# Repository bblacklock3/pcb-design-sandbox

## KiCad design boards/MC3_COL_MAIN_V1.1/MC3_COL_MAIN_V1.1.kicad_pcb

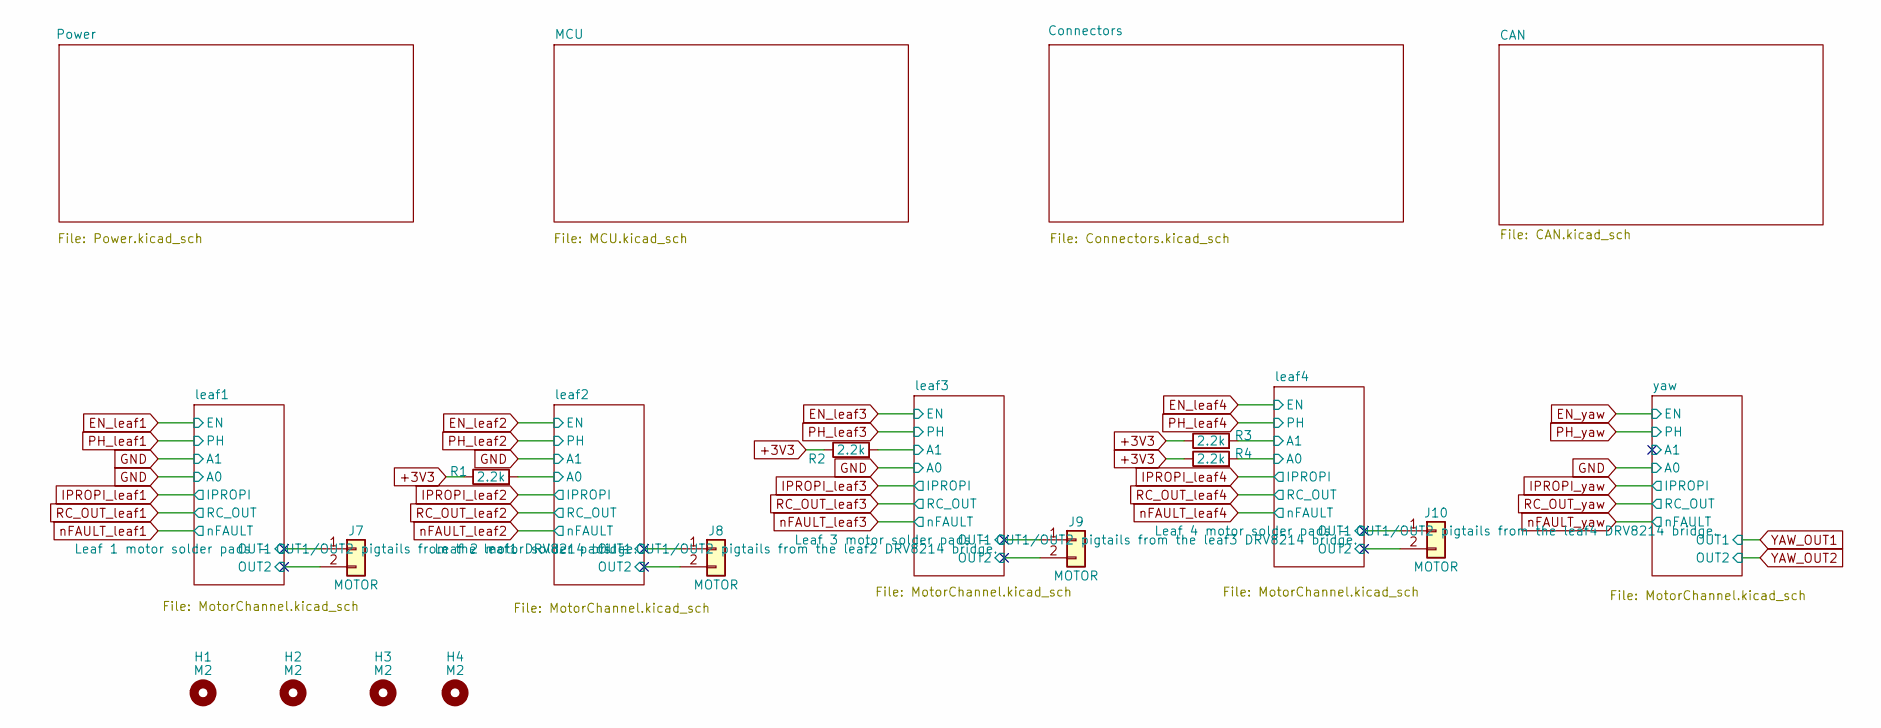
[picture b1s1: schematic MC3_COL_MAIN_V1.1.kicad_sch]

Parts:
H1, H2, H3, H4: M2; MountingHole_2.2mm_M2
J7, J8, J9, J10: MOTOR; SolderPads_2x_2.2x1.4mm_P2.6mm
R1, R2, R3, R4: 2.2k; R_0402_1005Metric; MPN 0402WGF2201TCE; LCSC C25879

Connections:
/leaf1/OUT1: J7.1; also elsewhere on the board
/leaf1/OUT2: J7.2; also elsewhere on the board
/leaf2/A0: R1.2; also elsewhere on the board
/leaf2/OUT1: J8.1; also elsewhere on the board
/leaf2/OUT2: J8.2; also elsewhere on the board
/leaf3/A1: R2.2; also elsewhere on the board
/leaf3/OUT1: J9.1; also elsewhere on the board
/leaf3/OUT2: J9.2; also elsewhere on the board
/leaf4/A0: R4.2; also elsewhere on the board
/leaf4/A1: R3.2; also elsewhere on the board
/leaf4/OUT1: J10.1; also elsewhere on the board
/leaf4/OUT2: J10.2; also elsewhere on the board

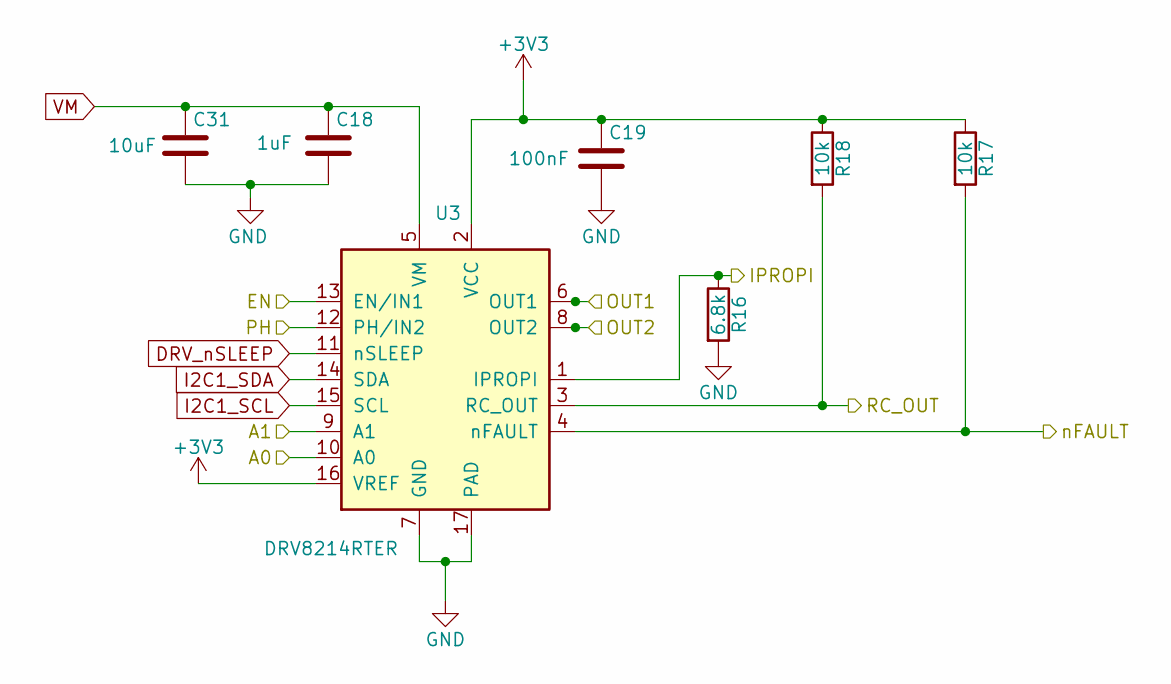
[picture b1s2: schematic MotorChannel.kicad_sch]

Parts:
C18: 1uF; C_0603_1608Metric; MPN CL10A105KB8NNNC; LCSC C15849
C19: 100nF; C_0402_1005Metric; MPN CL05B104KO5NNNC; LCSC C1525
C31: 10uF; C_0805_2012Metric; MPN CL21A106KAYNNNE; LCSC C15850
R16: 6.8k; R_0402_1005Metric; MPN RC0402FR-076K8L; LCSC C93940
R17, R18: 10k; R_0402_1005Metric; MPN 0402WGF1002TCE; LCSC C25744
U3: DRV8214RTER; WQFN-16-1EP_3x3mm_P0.5mm_EP1.68x1.68mm_ThermalVias; MPN DRV8214RTER; LCSC C22427938

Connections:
/leaf1/OUT1: U3.6 (OUT1); also elsewhere on the board
/leaf1/OUT2: U3.8 (OUT2); also elsewhere on the board
DRV_nSLEEP: U3.11 (nSLEEP); also elsewhere on the board
EN_leaf1: U3.13 (EN/IN1); also elsewhere on the board
I2C1_SCL: U3.15 (SCL); also elsewhere on the board
I2C1_SDA: U3.14 (SDA); also elsewhere on the board
IPROPI_leaf1: R16.1, U3.1 (IPROPI); also elsewhere on the board
PH_leaf1: U3.12 (PH/IN2); also elsewhere on the board
RC_OUT_leaf1: R18.2, U3.3 (RC_OUT); also elsewhere on the board
nFAULT_leaf1: R17.2, U3.4 (nFAULT); also elsewhere on the board

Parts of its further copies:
C20, C22, C24, C26: 1uF; C_0603_1608Metric; MPN CL10A105KB8NNNC; LCSC C15849
C21, C23, C25, C27: 100nF; C_0402_1005Metric; MPN CL05B104KO5NNNC; LCSC C1525
C33, C34, C35, C36: 10uF; C_0805_2012Metric; MPN CL21A106KAYNNNE; LCSC C15850
R19, R22, R25, R28: 6.8k; R_0402_1005Metric; MPN RC0402FR-076K8L; LCSC C93940
R20, R21, R23, R24, R26, R27, R29, R30: 10k; R_0402_1005Metric; MPN 0402WGF1002TCE; LCSC C25744
U4, U5, U6, U7: DRV8214RTER; WQFN-16-1EP_3x3mm_P0.5mm_EP1.68x1.68mm_ThermalVias; MPN DRV8214RTER; LCSC C22427938

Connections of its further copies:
/leaf2/A0: U4.10 (A0); also elsewhere on the board
/leaf2/OUT1: U4.6 (OUT1); also elsewhere on the board
/leaf2/OUT2: U4.8 (OUT2); also elsewhere on the board
/leaf3/A1: U5.9 (A1); also elsewhere on the board
/leaf3/OUT1: U5.6 (OUT1); also elsewhere on the board
/leaf3/OUT2: U5.8 (OUT2); also elsewhere on the board
/leaf4/A0: U6.10 (A0); also elsewhere on the board
/leaf4/A1: U6.9 (A1); also elsewhere on the board
/leaf4/OUT1: U6.6 (OUT1); also elsewhere on the board
/leaf4/OUT2: U6.8 (OUT2); also elsewhere on the board
/yaw/A1: U7.9 (A1)
DRV_nSLEEP: U4.11 (nSLEEP), U5.11 (nSLEEP), U6.11 (nSLEEP), U7.11 (nSLEEP); also elsewhere on the board
EN_leaf2: U4.13 (EN/IN1); also elsewhere on the board
EN_leaf3: U5.13 (EN/IN1); also elsewhere on the board
EN_leaf4: U6.13 (EN/IN1); also elsewhere on the board
EN_yaw: U7.13 (EN/IN1); also elsewhere on the board
I2C1_SCL: U4.15 (SCL), U5.15 (SCL), U6.15 (SCL), U7.15 (SCL); also elsewhere on the board
I2C1_SDA: U4.14 (SDA), U5.14 (SDA), U6.14 (SDA), U7.14 (SDA); also elsewhere on the board
IPROPI_leaf2: R19.1, U4.1 (IPROPI); also elsewhere on the board
IPROPI_leaf3: R22.1, U5.1 (IPROPI); also elsewhere on the board
IPROPI_leaf4: R25.1, U6.1 (IPROPI); also elsewhere on the board
IPROPI_yaw: R28.1, U7.1 (IPROPI); also elsewhere on the board
PH_leaf2: U4.12 (PH/IN2); also elsewhere on the board
PH_leaf3: U5.12 (PH/IN2); also elsewhere on the board
PH_leaf4: U6.12 (PH/IN2); also elsewhere on the board
PH_yaw: U7.12 (PH/IN2); also elsewhere on the board
RC_OUT_leaf2: R21.2, U4.3 (RC_OUT); also elsewhere on the board
RC_OUT_leaf3: R24.2, U5.3 (RC_OUT); also elsewhere on the board
RC_OUT_leaf4: R27.2, U6.3 (RC_OUT); also elsewhere on the board
RC_OUT_yaw: R30.2, U7.3 (RC_OUT); also elsewhere on the board
YAW_OUT1: U7.6 (OUT1); also elsewhere on the board
YAW_OUT2: U7.8 (OUT2); also elsewhere on the board
nFAULT_leaf2: R20.2, U4.4 (nFAULT); also elsewhere on the board
nFAULT_leaf3: R23.2, U5.4 (nFAULT); also elsewhere on the board
nFAULT_leaf4: R26.2, U6.4 (nFAULT); also elsewhere on the board
nFAULT_yaw: R29.2, U7.4 (nFAULT); also elsewhere on the board

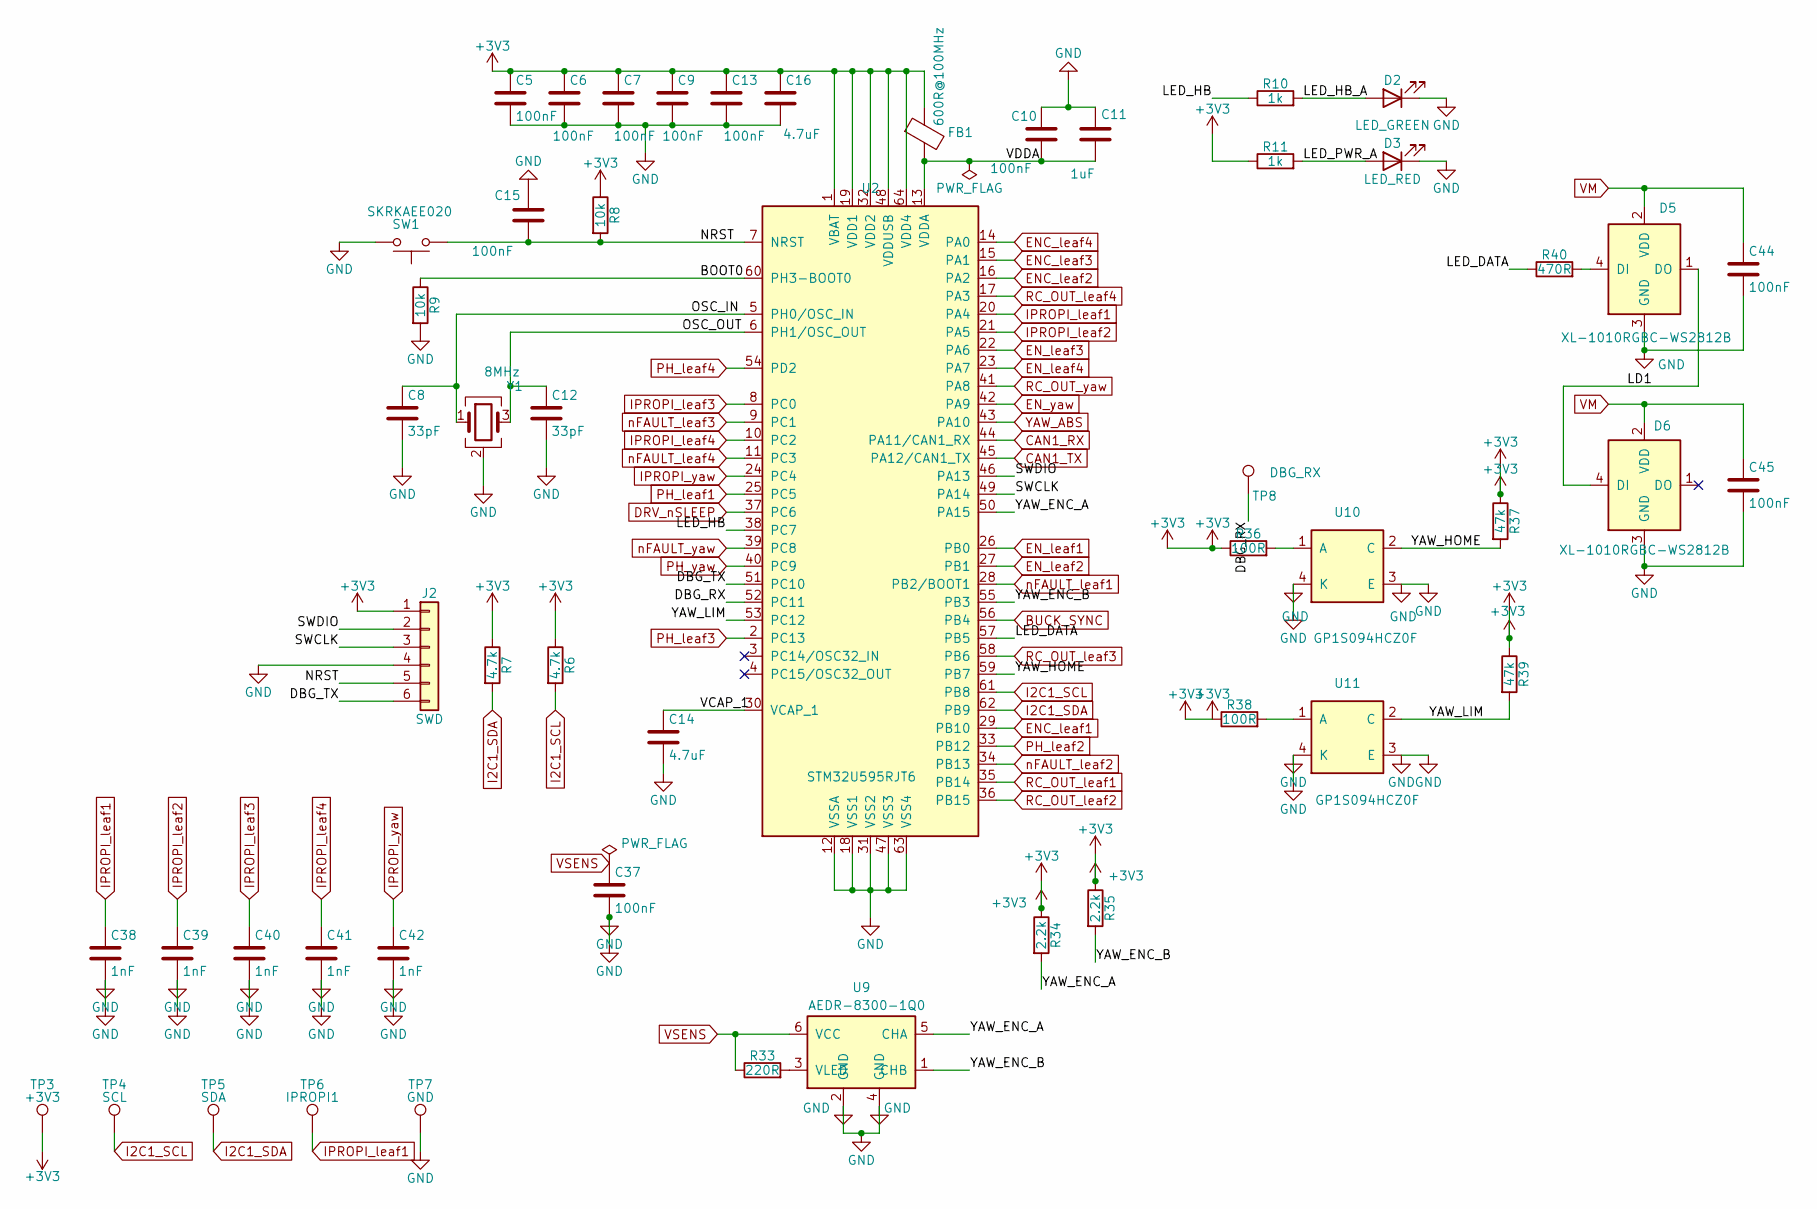
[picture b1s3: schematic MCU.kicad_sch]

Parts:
C5, C6, C7, C9, C10, C13, C15: 100nF; C_0402_1005Metric; MPN CL05B104KO5NNNC; LCSC C1525
C8, C12: 33pF; C_0402_1005Metric; MPN 0402CG330J500NT; LCSC C1562
C11: 1uF; C_0402_1005Metric; MPN CL05A105KA5NQNC; LCSC C52923
C14: 4.7uF; C_0603_1608Metric; MPN CL10A475KO8NNNC; LCSC C19666
C16: 4.7uF; C_0805_2012Metric; MPN CL21A475KAQNNNE; LCSC C1779
C37, C44, C45: 100nF; C_0402_1005Metric; LCSC C1525
C38, C39, C40, C41, C42: 1nF; C_0402_1005Metric; LCSC C1523
D2: LED_GREEN; LED_0603_1608Metric; MPN KT-0603G; LCSC C12624
D3: LED_RED; LED_0603_1608Metric; MPN KT-0603R; LCSC C2286
D5, D6: XL-1010RGBC-WS2812B; LED_XL-1010RGBC; MPN XL-1010RGBC-WS2812B; LCSC C5349953
FB1: 600R@100MHz; L_0603_1608Metric; MPN GZ1608D601TF; LCSC C1002
J2: SWD; PinHeader_1x06_P2.54mm_Vertical
R6, R7: 4.7k; R_0402_1005Metric; MPN 0402WGF4701TCE; LCSC C25900
R8, R9: 10k; R_0402_1005Metric; MPN 0402WGF1002TCE; LCSC C25744
R10, R11: 1k; R_0402_1005Metric; MPN 0402WGF1001TCE; LCSC C11702
R33: 220R; R_0402_1005Metric; LCSC C25091
R34, R35: 2.2k; R_0402_1005Metric; LCSC C25879
R36, R38: 100R; R_0402_1005Metric; LCSC C25076
R37, R39: 47k; R_0402_1005Metric; LCSC C25792
R40: 470R; R_0402_1005Metric; LCSC C25117
SW1: SKRKAEE020; SW_Push_SPST_NO_Alps_SKRK; MPN SKRKAEE020; LCSC C115357
TP3: +3V3; TestPoint_Pad_1.0x1.0mm
TP4: SCL; TestPoint_Pad_1.0x1.0mm
TP5: SDA; TestPoint_Pad_1.0x1.0mm
TP6: IPROPI1; TestPoint_Pad_1.0x1.0mm
TP7: GND; TestPoint_Pad_1.0x1.0mm
TP8: DBG_RX; TestPoint_Pad_1.0x1.0mm
U2: STM32U595RJT6; LQFP-64_10x10mm_P0.5mm; MPN STM32U595RJT6
U9: AEDR-8300-1Q0; AEDR-8300; MPN AEDR-8300-1Q0; LCSC C22453800
U10, U11: GP1S094HCZ0F; MPN GP1S094HCZ0F; LCSC C920601
Y1: 8MHz; Crystal_SMD_3225-4Pin_3.2x2.5mm; MPN X32258MSB4SI; LCSC C2682774

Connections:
/MCU/BOOT0: R9.1, U2.60 (PH3-BOOT0)
/MCU/DBG_RX: TP8.1 (1_1), U2.52 (PC11)
/MCU/DBG_TX: J2.6, U2.51 (PC10)
/MCU/LD1: D5.1 (DO), D6.4 (DI)
/MCU/LED_DATA: R40.1, U2.57 (PB5)
/MCU/LED_HB: R10.1, U2.38 (PC7)
/MCU/LED_HB_A: D2.2 (A), R10.2
/MCU/LED_PWR_A: D3.2 (A), R11.2
/MCU/NRST: C15.1, J2.5, R8.2, SW1.1, U2.7 (NRST)
/MCU/OSC_IN: C8.1, U2.5 (PH0/OSC_IN), Y1.1
/MCU/OSC_OUT: C12.1, U2.6 (PH1/OSC_OUT), Y1.3
/MCU/SWCLK: J2.3, U2.49 (PA14)
/MCU/SWDIO: J2.2, U2.46 (PA13)
/MCU/VCAP_1: C14.1, U2.30 (VCAP_1)
/MCU/YAW_ENC_A: R34.2, U2.50 (PA15), U9.5 (CHA)
/MCU/YAW_ENC_B: R35.2, U2.55 (PB3), U9.1 (CHB)
/MCU/YAW_HOME: R37.2, U2.59 (PB7), U10.2 (C)
/MCU/YAW_LIM: R39.2, U2.53 (PC12), U11.2 (C)
BUCK_SYNC: U2.56 (PB4); also elsewhere on the board
CAN1_RX: U2.44 (PA11/CAN1_RX); also elsewhere on the board
CAN1_TX: U2.45 (PA12/CAN1_TX); also elsewhere on the board
DRV_nSLEEP: U2.37 (PC6); also elsewhere on the board
ENC_leaf1: U2.29 (PB10); also elsewhere on the board
ENC_leaf2: U2.16 (PA2); also elsewhere on the board
ENC_leaf3: U2.15 (PA1); also elsewhere on the board
ENC_leaf4: U2.14 (PA0); also elsewhere on the board
EN_leaf1: U2.26 (PB0); also elsewhere on the board
EN_leaf2: U2.27 (PB1); also elsewhere on the board
EN_leaf3: U2.22 (PA6); also elsewhere on the board
EN_leaf4: U2.23 (PA7); also elsewhere on the board
EN_yaw: U2.42 (PA9); also elsewhere on the board
I2C1_SCL: R6.2, TP4.1 (1_1), U2.61 (PB8); also elsewhere on the board
I2C1_SDA: R7.2, TP5.1 (1_1), U2.62 (PB9); also elsewhere on the board
IPROPI_leaf1: C38.1, TP6.1 (1_1), U2.20 (PA4); also elsewhere on the board
IPROPI_leaf2: C39.1, U2.21 (PA5); also elsewhere on the board
IPROPI_leaf3: C40.1, U2.8 (PC0); also elsewhere on the board
IPROPI_leaf4: C41.1, U2.10 (PC2); also elsewhere on the board
IPROPI_yaw: C42.1, U2.24 (PC4); also elsewhere on the board
unnamed: D5.4 (DI), R40.2
unnamed: R33.2, U9.3 (VLED)
unnamed: R36.2, U10.1 (A)
unnamed: R38.2, U11.1 (A)
PH_leaf1: U2.25 (PC5); also elsewhere on the board
PH_leaf2: U2.33 (PB12); also elsewhere on the board
PH_leaf3: U2.2 (PC13); also elsewhere on the board
PH_leaf4: U2.54 (PD2); also elsewhere on the board
PH_yaw: U2.40 (PC9); also elsewhere on the board
RC_OUT_leaf1: U2.35 (PB14); also elsewhere on the board
RC_OUT_leaf2: U2.36 (PB15); also elsewhere on the board
RC_OUT_leaf3: U2.58 (PB6); also elsewhere on the board
RC_OUT_leaf4: U2.17 (PA3); also elsewhere on the board
RC_OUT_yaw: U2.41 (PA8); also elsewhere on the board
YAW_ABS: U2.43 (PA10); also elsewhere on the board
nFAULT_leaf1: U2.28 (PB2/BOOT1); also elsewhere on the board
nFAULT_leaf2: U2.34 (PB13); also elsewhere on the board
nFAULT_leaf3: U2.9 (PC1); also elsewhere on the board
nFAULT_leaf4: U2.11 (PC3); also elsewhere on the board
nFAULT_yaw: U2.39 (PC8); also elsewhere on the board

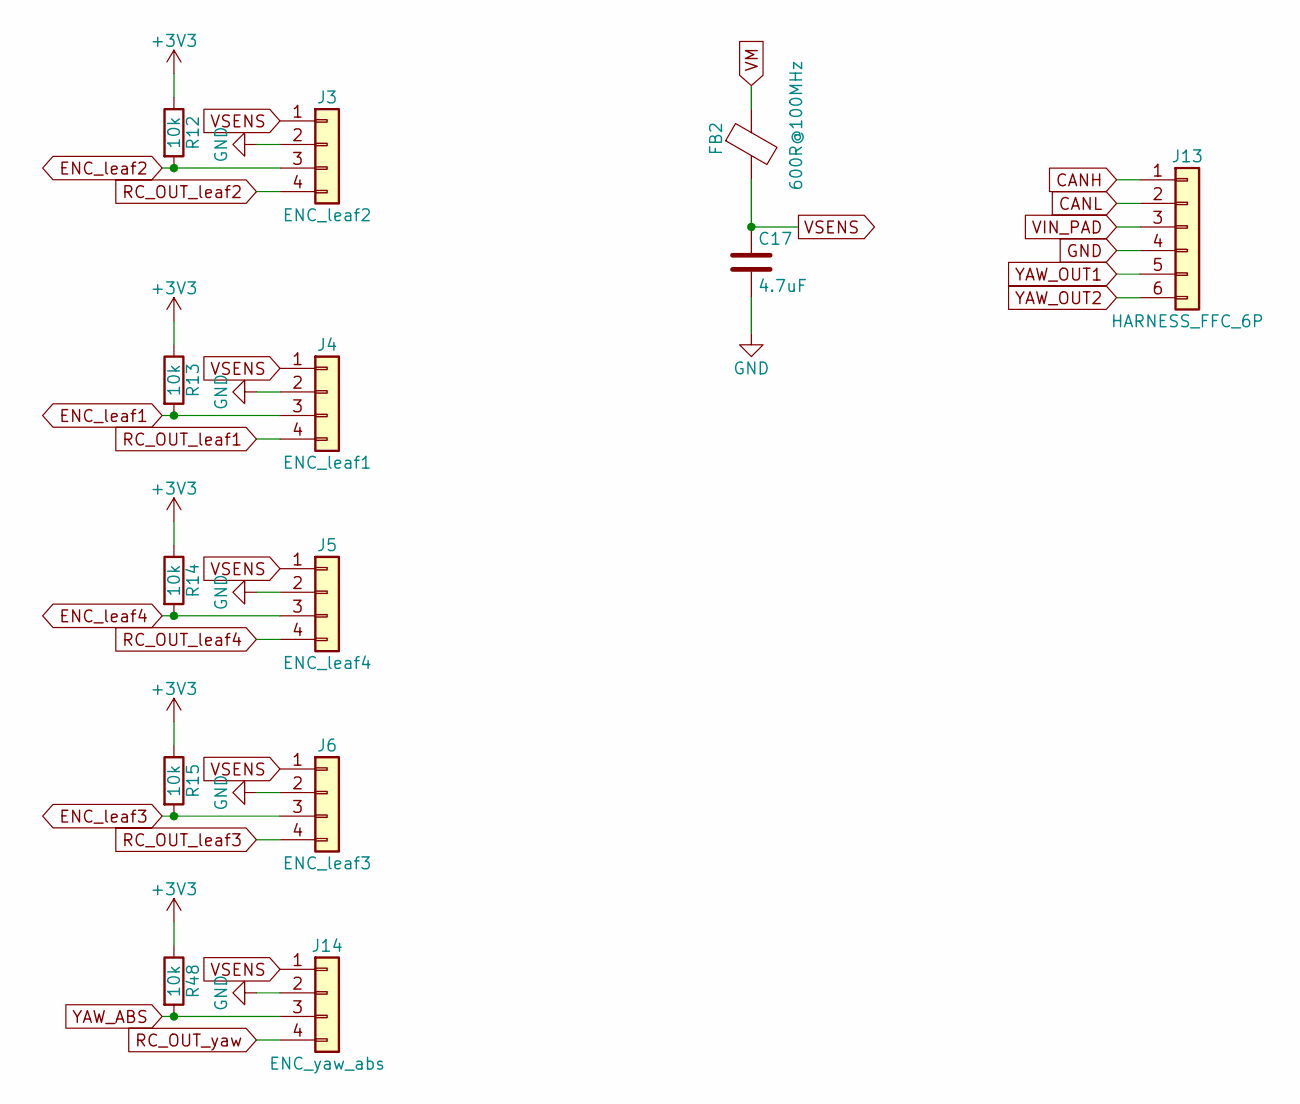
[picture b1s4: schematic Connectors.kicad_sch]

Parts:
C17: 4.7uF; C_0603_1608Metric; MPN CL10A475KO8NNNC; LCSC C19666
FB2: 600R@100MHz; L_0603_1608Metric; MPN GZ1608D601TF; LCSC C1002
J3: ENC_leaf2; Panasonic_AYF530435_FFC-4P_P0.5mm; MPN AYF530435; LCSC C425129
J4: ENC_leaf1; Panasonic_AYF530435_FFC-4P_P0.5mm; MPN AYF530435; LCSC C425129
J5: ENC_leaf4; Panasonic_AYF530435_FFC-4P_P0.5mm; MPN AYF530435; LCSC C425129
J6: ENC_leaf3; Panasonic_AYF530435_FFC-4P_P0.5mm; MPN AYF530435; LCSC C425129
J13: HARNESS_FFC_6P; TE_84952-6_1x06-1MP_P1.0mm_Horizontal; MPN 84952-6
J14: ENC_yaw_abs; Panasonic_AYF530435_FFC-4P_P0.5mm
R12, R13, R14, R15: 10k; R_0402_1005Metric; MPN 0402WGF1002TCE; LCSC C25744
R48: 10k; R_0402_1005Metric

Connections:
CANH: J13.1; also elsewhere on the board
CANL: J13.2; also elsewhere on the board
ENC_leaf1: J4.3, R13.2; also elsewhere on the board
ENC_leaf2: J3.3, R12.2; also elsewhere on the board
ENC_leaf3: J6.3, R15.2; also elsewhere on the board
ENC_leaf4: J5.3, R14.2; also elsewhere on the board
RC_OUT_leaf1: J4.4; also elsewhere on the board
RC_OUT_leaf2: J3.4; also elsewhere on the board
RC_OUT_leaf3: J6.4; also elsewhere on the board
RC_OUT_leaf4: J5.4; also elsewhere on the board
RC_OUT_yaw: J14.4; also elsewhere on the board
VIN_PAD: J13.3; also elsewhere on the board
YAW_ABS: J14.3, R48.2; also elsewhere on the board
YAW_OUT1: J13.5; also elsewhere on the board
YAW_OUT2: J13.6; also elsewhere on the board

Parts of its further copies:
R30: 10k; R_0402_1005Metric; MPN 0402WGF1002TCE; LCSC C25744

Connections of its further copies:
RC_OUT_yaw: R30.2; also elsewhere on the board

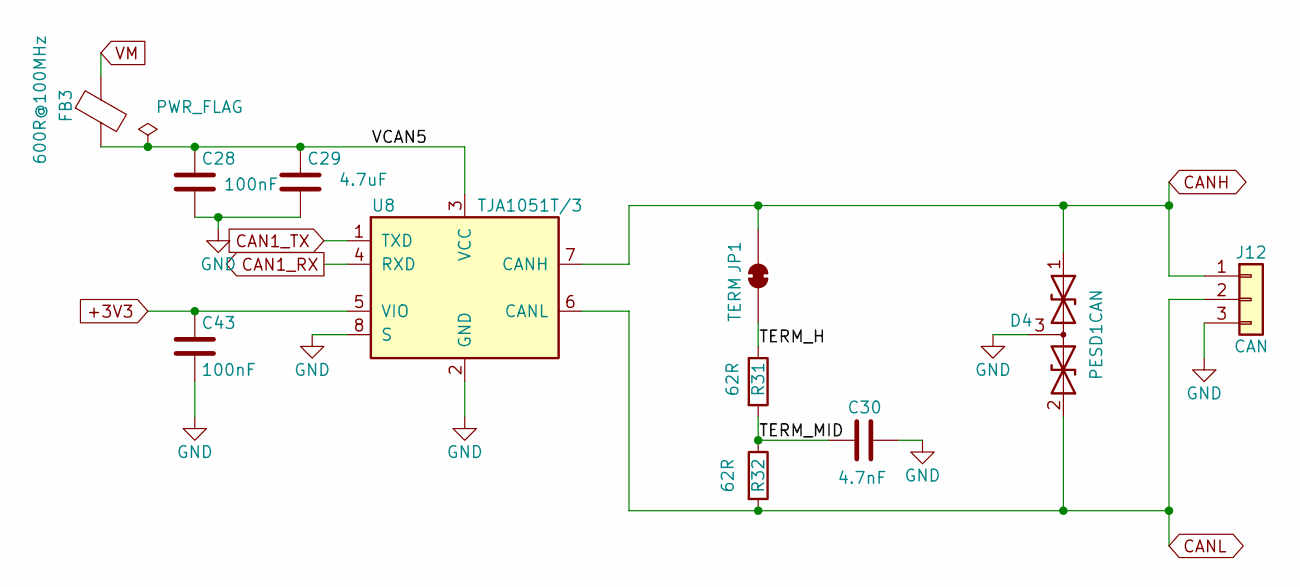
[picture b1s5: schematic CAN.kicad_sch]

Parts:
C28: 100nF; C_0402_1005Metric; MPN CL05B104KO5NNNC; LCSC C1525
C29: 4.7uF; C_0603_1608Metric; MPN CL10A475KO8NNNC; LCSC C19666
C30: 4.7nF; C_0402_1005Metric; MPN 0402B472K500NT; LCSC C1538
C43: 100nF; C_0402_1005Metric; LCSC C1525
D4: PESD1CAN; SOT-23; MPN PESD1CAN,215; LCSC C15771
FB3: 600R@100MHz; L_0603_1608Metric; MPN GZ1608D601TF; LCSC C1002
J12: CAN; SolderPads_3x_2.2x1.4mm_P2.6mm
JP1: TERM; SolderJumper-2_P1.3mm_Bridged_RoundedPad1.0x1.5mm
R31, R32: 62R; R_0402_1005Metric; MPN 0402WGF620JTCE; LCSC C4962
U8: TJA1051T/3; SOIC-8_3.9x4.9mm_P1.27mm; MPN TJA1051T/3/1J; LCSC C38695

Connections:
/CAN/TERM_H: JP1.2 (B), R31.1
/CAN/TERM_MID: C30.1, R31.2, R32.1
/CAN/VCAN5: C28.1, C29.1, FB3.2, U8.3 (VCC)
CAN1_RX: U8.4 (RXD); also elsewhere on the board
CAN1_TX: U8.1 (TXD); also elsewhere on the board
CANH: D4.1 (A1), J12.1, JP1.1 (A), U8.7 (CANH); also elsewhere on the board
CANL: D4.2 (A2), J12.2, R32.2, U8.6 (CANL); also elsewhere on the board

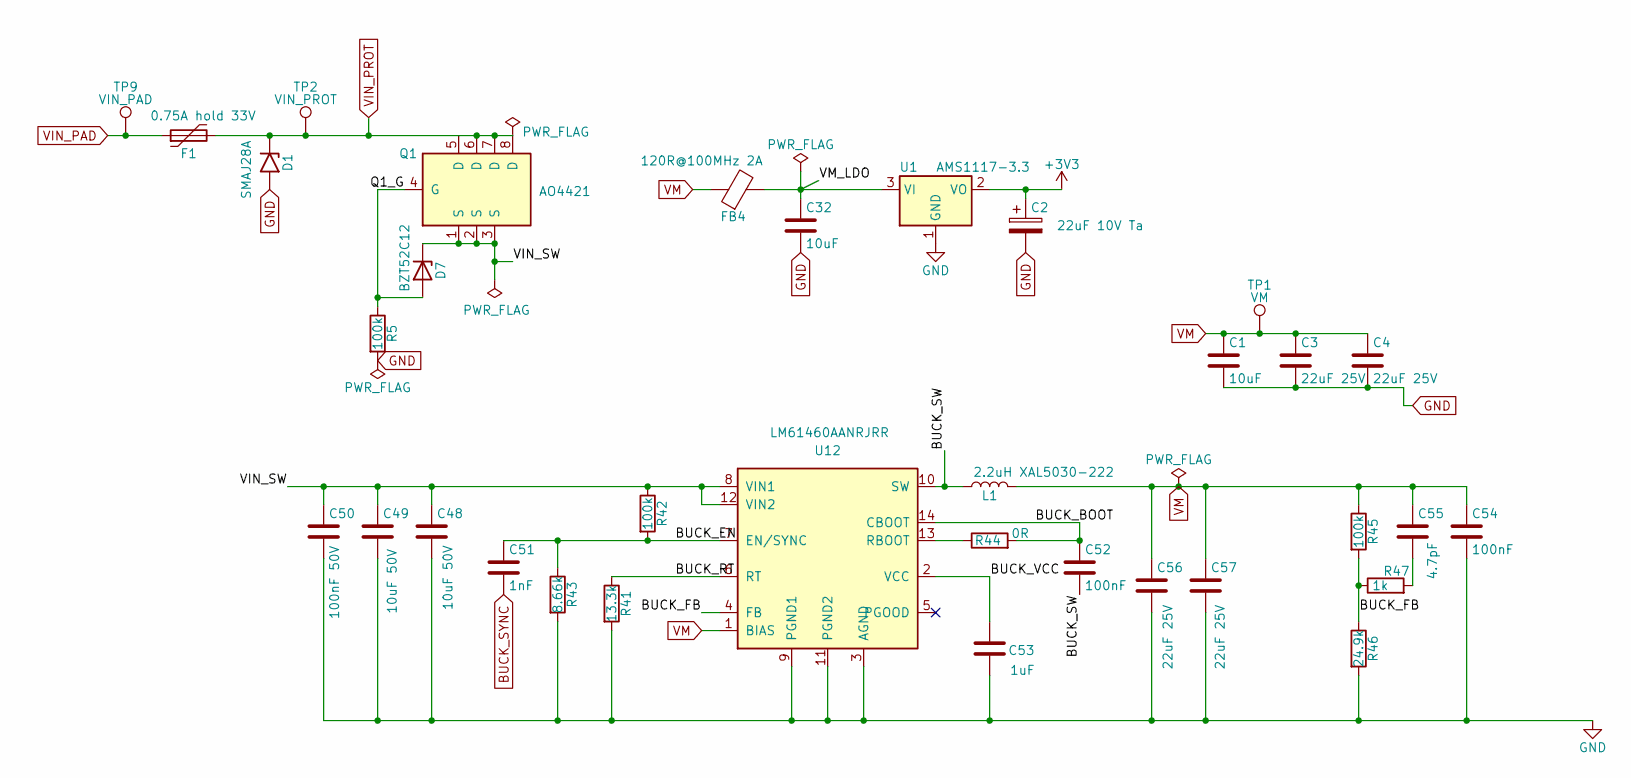
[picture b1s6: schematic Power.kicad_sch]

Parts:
C1, C32: 10uF; C_0805_2012Metric; MPN CL21A106KAYNNNE; LCSC C15850
C2: 22uF 10V Ta; CP_EIA-3216-18_Kemet-A; MPN TAJA226K010RNJ; LCSC C11366
C3, C4, C56, C57: 22uF 25V; C_0805_2012Metric; MPN CL21A226MAQNNNE; LCSC C45783
C48, C49: 10uF 50V; C_1210_3225Metric; MPN GRM32ER71H106KA12L
C50: 100nF 50V; C_0603_1608Metric; MPN CL10B104KB8NNNC; LCSC C1591
C51: 1nF; C_0402_1005Metric; LCSC C1523
C52, C54: 100nF; C_0402_1005Metric; MPN CL05B104KO5NNNC; LCSC C1525
C53: 1uF; C_0603_1608Metric; MPN CL10A105KB8NNNC; LCSC C15849
C55: 4.7pF; C_0402_1005Metric; MPN 0402CG4R7C500NT
D1: SMAJ28A; D_SMA; MPN SMAJ28A
D7: BZT52C12; D_SOD-123; MPN BZT52C12
F1: 0.75A hold 33V; Fuse_1812_4532Metric; MPN 1812L075/33DR; LCSC C151170
FB4: 120R@100MHz 2A; L_0603_1608Metric; MPN BLM18PG121SN1D; LCSC C14709
L1: 2.2uH XAL5030-222; L_Coilcraft_XAL5030-XXX; MPN XAL5030-222MEB
Q1: AO4421; SOIC-8_3.9x4.9mm_P1.27mm; MPN AO4421; LCSC C33484
R5, R42, R45: 100k; R_0402_1005Metric; MPN 0402WGF1003TCE; LCSC C25741
R41: 13.3k; R_0402_1005Metric; MPN 0402WGF1332TCE
R43: 8.66k; R_0402_1005Metric; MPN 0402WGF8661TCE
R44: 0R; R_0402_1005Metric; MPN 0402WGF0000TCE
R46: 24.9k; R_0402_1005Metric; MPN 0402WGF2492TCE
R47: 1k; R_0402_1005Metric; MPN 0402WGF1001TCE; LCSC C11702
TP1: VM; TestPoint_Pad_1.0x1.0mm
TP2: VIN_PROT; TestPoint_Pad_1.0x1.0mm
TP9: VIN_PAD; TestPoint_Pad_1.0x1.0mm
U1: AMS1117-3.3; SOT-223-3_TabPin2; MPN AMS1117-3.3; LCSC C6186
U12: LM61460AANRJRR; VQFN-HR14_RJR_TEX; MPN LM61460AANRJRR; LCSC C2864505

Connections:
/Power/BUCK_BOOT: C52.1, R44.2, U12.14 (CBOOT)
/Power/BUCK_EN: C51.1, R42.2, R43.1, U12.7 (EN/SYNC)
/Power/BUCK_FB: R45.2, R46.1, R47.1, U12.4 (FB)
/Power/BUCK_RT: R41.1, U12.6 (RT)
/Power/BUCK_SW: C52.2, L1.1, U12.10 (SW)
/Power/BUCK_VCC: C53.1, U12.2 (VCC)
/Power/Q1_G: D7.2 (A), Q1.4 (G), R5.1
BUCK_SYNC: C51.2; also elsewhere on the board
unnamed: C55.2, R47.2
unnamed: R44.1, U12.13 (RBOOT)
VIN_PAD: F1.1, TP9.1 (1_1); also elsewhere on the board

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
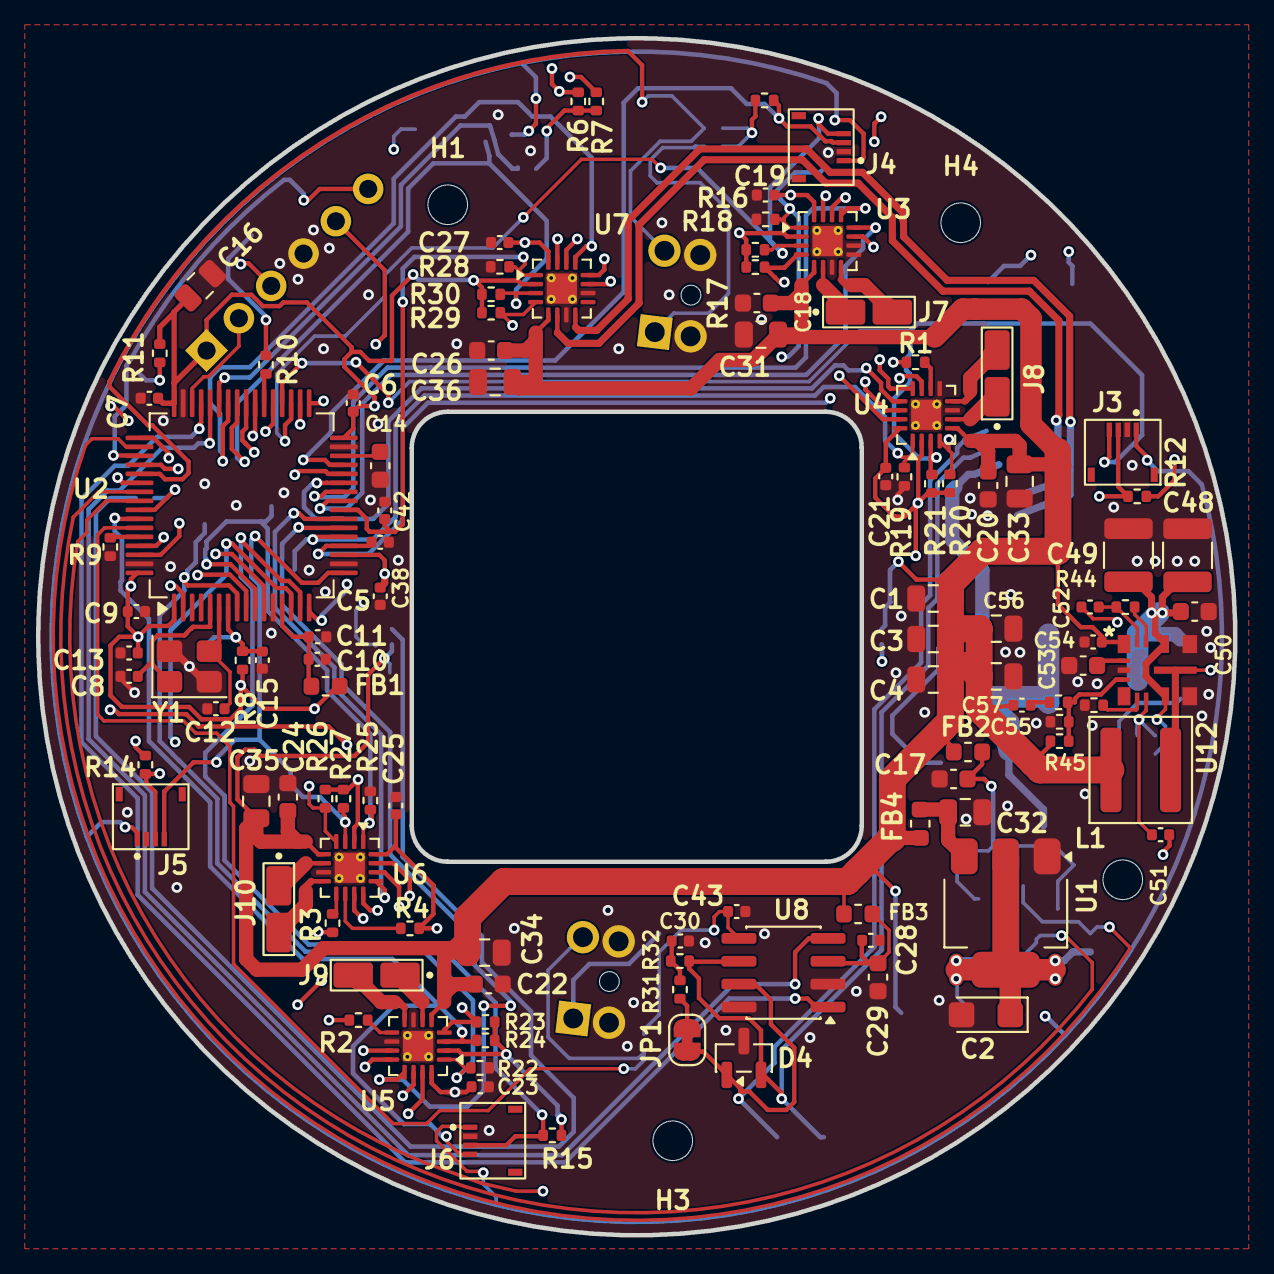
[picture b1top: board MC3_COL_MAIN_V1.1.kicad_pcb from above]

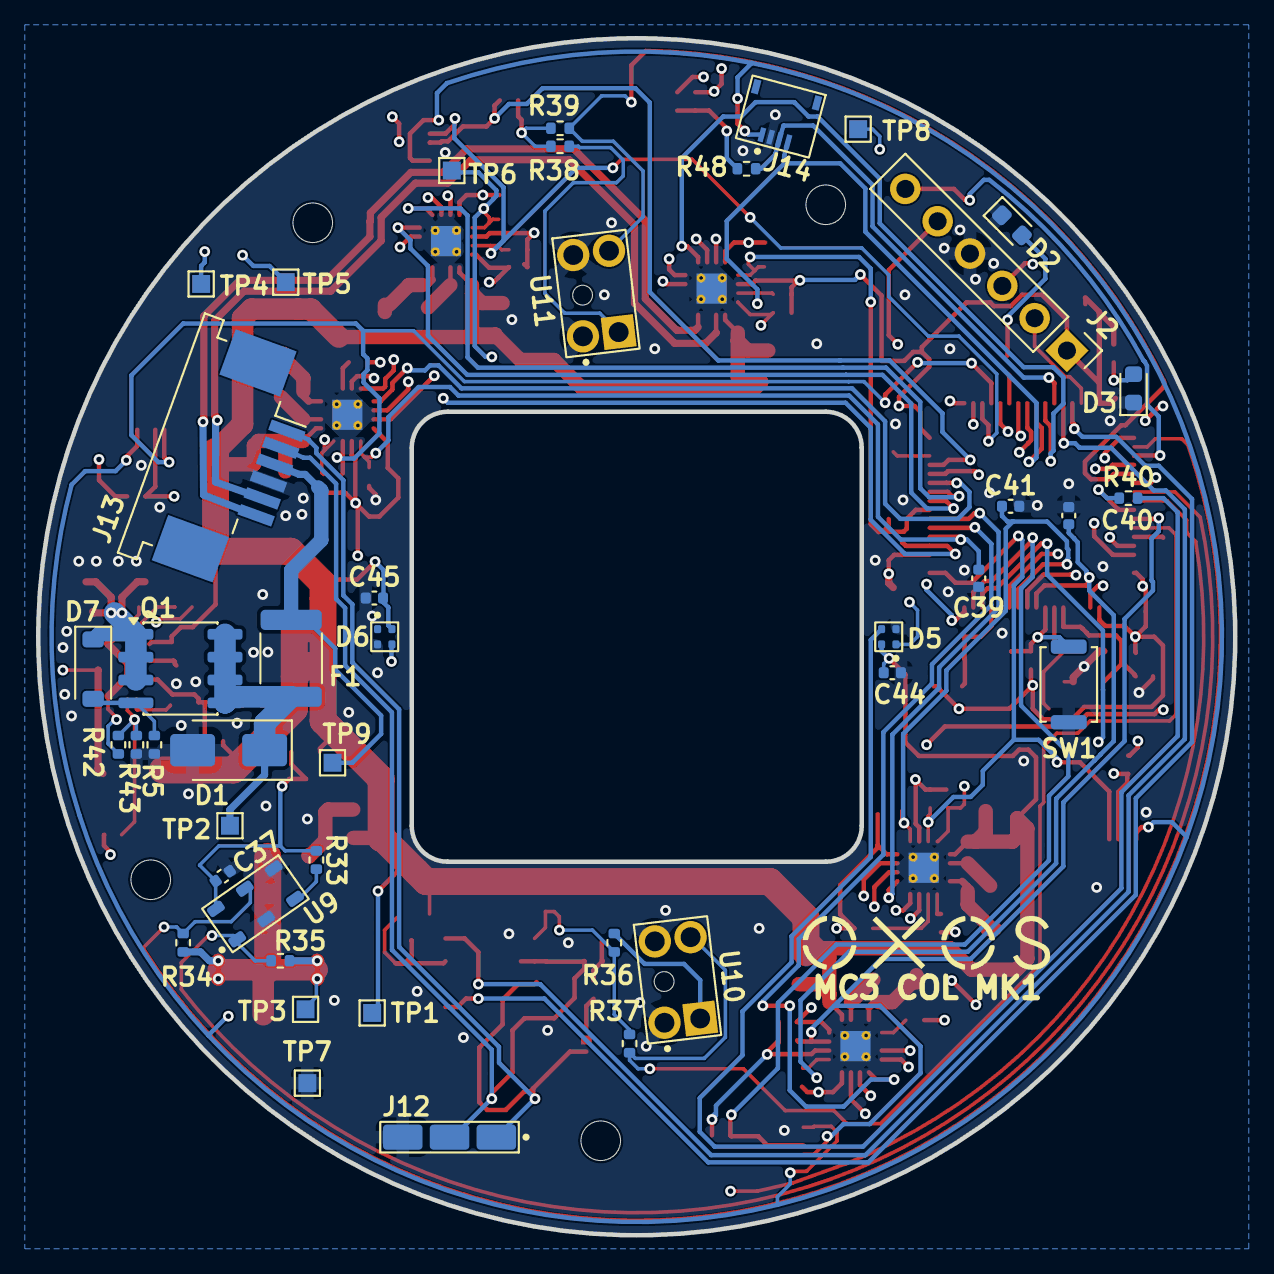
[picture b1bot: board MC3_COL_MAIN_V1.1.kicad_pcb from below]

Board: 4 copper layers, 66.5 x 66.5 mm, 158 parts (45 on the bottom side), 95 nets.

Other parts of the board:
G8: LOGO; OXOS_Logo_Big

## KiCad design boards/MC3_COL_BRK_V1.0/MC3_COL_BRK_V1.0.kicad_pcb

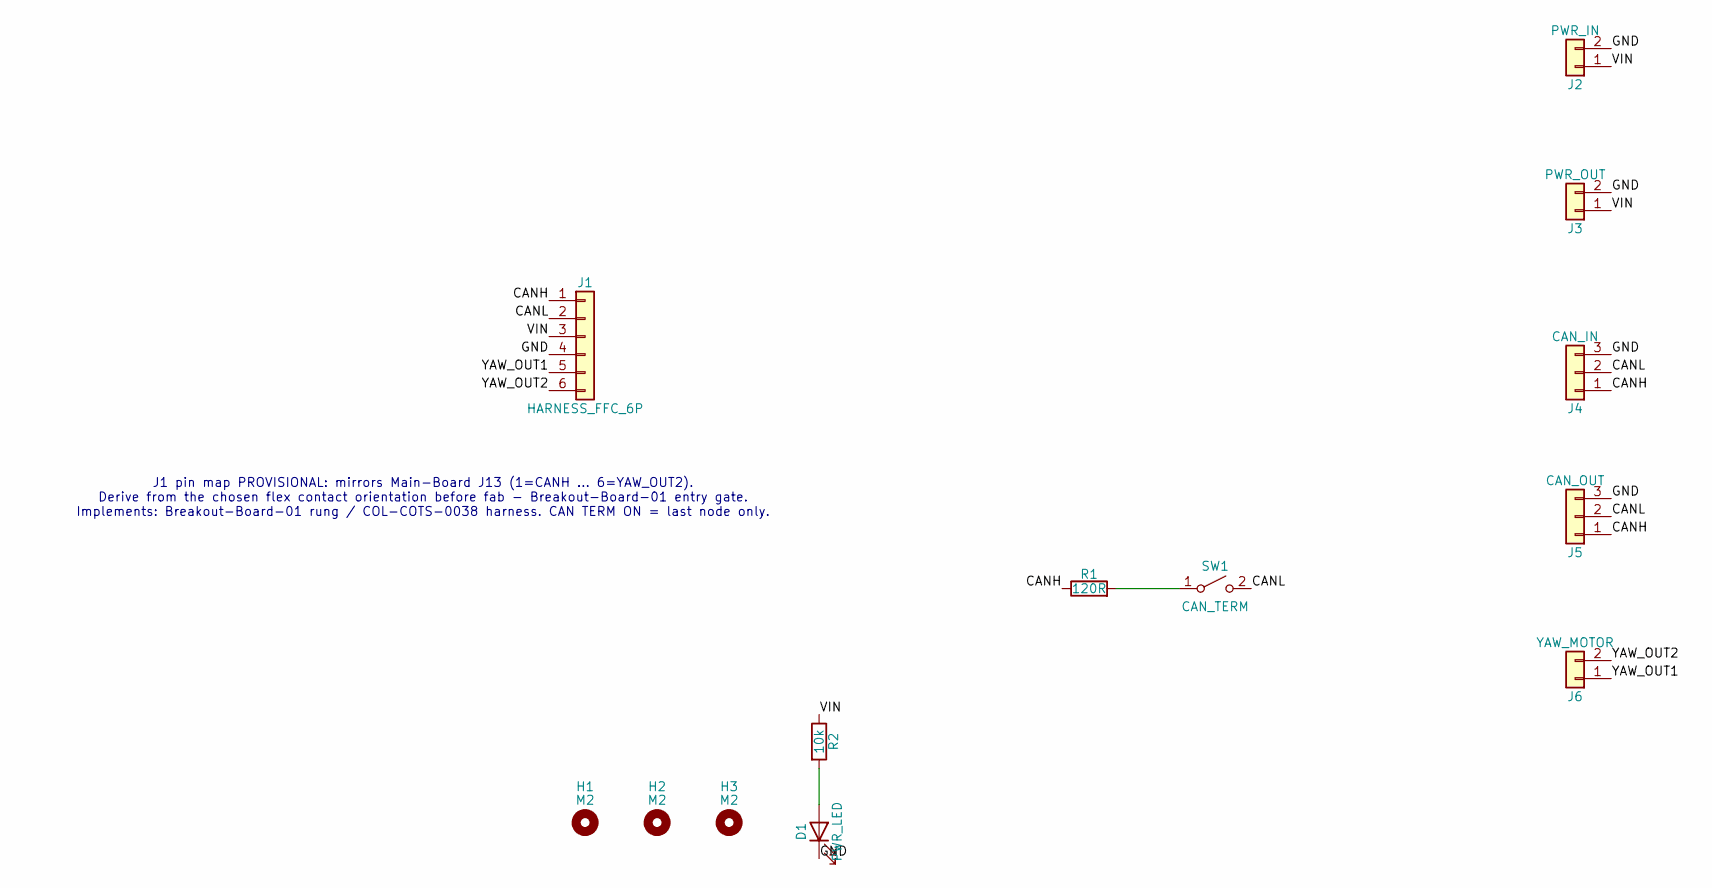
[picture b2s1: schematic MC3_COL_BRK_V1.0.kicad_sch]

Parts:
D1: PWR_LED; LED_0603_1608Metric
H1, H2, H3: M2; MountingHole_2.2mm_M2
J1: HARNESS_FFC_6P; TE_84952-6_1x06-1MP_P1.0mm_Horizontal
J2: PWR_IN; JST_XH_B2B-XH-A_1x02_P2.50mm_Vertical; MPN B2B-XH-A
J3: PWR_OUT; JST_XH_B2B-XH-A_1x02_P2.50mm_Vertical; MPN B2B-XH-A
J4: CAN_IN; JST_XH_B3B-XH-A_1x03_P2.50mm_Vertical; MPN B3B-XH-A
J5: CAN_OUT; JST_XH_B3B-XH-A_1x03_P2.50mm_Vertical; MPN B3B-XH-A
J6: YAW_MOTOR; JST_XH_B2B-XH-A_1x02_P2.50mm_Vertical; MPN B2B-XH-A
R1: 120R; R_0603_1608Metric
R2: 10k; R_0603_1608Metric
SW1: CAN_TERM; SW_DIP_SPSTx01_Slide_6.7x4.1mm_W8.61mm_P2.54mm_LowProfile

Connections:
/CANH: J1.1, J4.1, J5.1, R1.1
/CANL: J1.2, J4.2, J5.2, SW1.2 (B)
/GND: D1.1 (K), J1.4, J2.2, J3.2, J4.3, J5.3
/VIN: J1.3, J2.1, J3.1, R2.1
/YAW_OUT1: J1.5, J6.1
/YAW_OUT2: J1.6, J6.2
unnamed: D1.2 (A), R2.2
unnamed: R1.2, SW1.1 (A)

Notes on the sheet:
J1 pin map PROVISIONAL: mirrors Main-Board J13 (1=CANH ... 6=YAW_OUT2). Derive from the chosen flex contact orientation before fab - Breakout-Board-01 entry gate. Implements: Breakout-Board-01 rung / COL-COTS-0038 harness. CAN TERM ON = last node only.

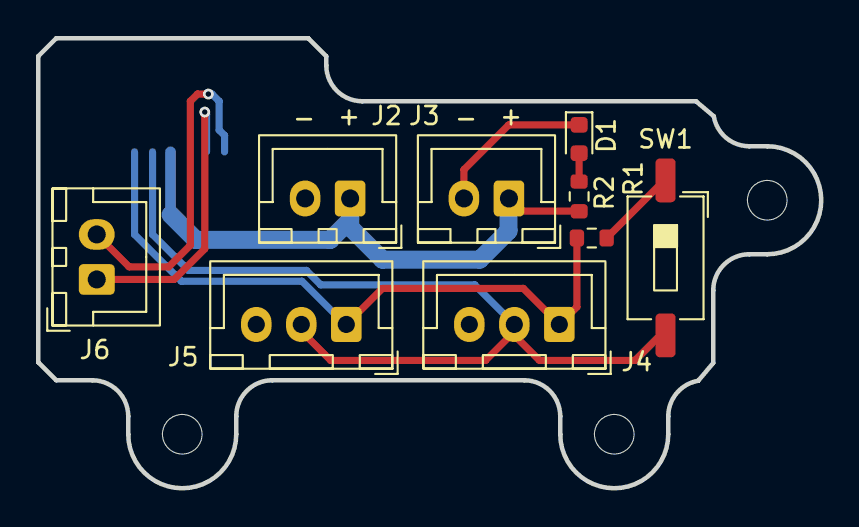
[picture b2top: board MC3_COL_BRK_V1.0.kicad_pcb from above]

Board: 2 copper layers, 43.5 x 25.0 mm, 13 parts (1 on the bottom side), 8 nets.

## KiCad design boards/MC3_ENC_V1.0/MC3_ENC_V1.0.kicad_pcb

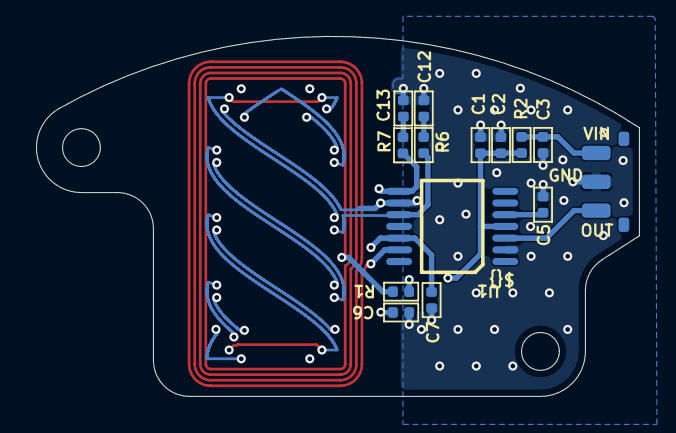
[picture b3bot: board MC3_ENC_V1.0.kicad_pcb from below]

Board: 4 copper layers, 33.5 x 20.0 mm, 16 parts (16 on the bottom side), 10 nets.

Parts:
C1: 1nF; 0402_Cap
C2, C3, C5: 100nF; 0402_Cap
C6, C7: 1200pF; 0402_Cap
C12, C13: 4.7nF; 0402_Cap
L5, L6, L7: PCB L; JMP
R1: 10; 0402_Res
R2: 4.7 OHM; 0402_Res
R6, R7: 4.7R; 0402_Res
U1: LX34312/LX34311; TSSOP-14

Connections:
/CL1: R7.2, U1.8 (CL1)
/CL2: R6.2, U1.10 (CL2)
/OSC1: C6.1, U1.13 (OSC1)
/OSC2: C7.1, U1.12 (OSC2)
/VIN_EXT: C3.2, R2.1
GND: C1.1, C2.1, C3.1, C5.2, C6.2, C7.2, C12.2, C13.2, L6.1, L7.1, U1.2 (AGND), U1.9 (GNDCL)
unnamed: C12.1, R6.1
unnamed: C13.1, R7.1
VDD: C5.1, U1.5 (VDD)
VIN: C1.2, C2.2, R1.1, R2.2, U1.4 (VIN)
